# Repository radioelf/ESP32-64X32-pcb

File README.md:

# ESP32-64X32-pcb
PCB para conectar un ESP32 (ESP32-DevKitC) a un panel de 64x32 pixels (p5(2121)-16S-6432-B0), siguiendo
el proyecto de [domótica fácil con Jota](https://www.youtube.com/channel/UC61-AfFnspjffs71zmmn2Ig)

Creative Commons License Disclaimer

UNLESS OTHERWISE MUTUALLY AGREED TO BY THE PARTIES IN WRITING, LICENSOR OFFERS THE WORK AS-IS AND MAKES NO REPRESENTATIONS OR WARRANTIES OF ANY KIND CONCERNING THE WORK, EXPRESS, IMPLIED, STATUTORY OR OTHERWISE, INCLUDING, WITHOUT LIMITATION, WARRANTIES OF TITLE, MERCHANTIBILITY, FITNESS FOR A PARTICULAR PURPOSE, NONINFRINGEMENT, OR THE ABSENCE OF LATENT OR OTHER DEFECTS, ACCURACY, OR THE PRESENCE OF ABSENCE OF ERRORS, WHETHER OR NOT DISCOVERABLE. SOME JURISDICTIONS DO NOT ALLOW THE EXCLUSION OF IMPLIED WARRANTIES, SO SUCH EXCLUSION MAY NOT APPLY TO YOU. EXCEPT TO THE EXTENT REQUIRED BY APPLICABLE LAW, IN NO EVENT WILL LICENSOR BE LIABLE TO YOU ON ANY LEGAL THEORY FOR ANY SPECIAL, INCIDENTAL, CONSEQUENTIAL, PUNITIVE OR EXEMPLARY DAMAGES ARISING OUT OF THIS LICENSE OR THE USE OF THE WORK, EVEN IF LICENSOR HAS BEEN ADVISED OF THE POSSIBILITY OF SUCH DAMAGES.

http://creativecommons.org/licenses/by-sa/3.0/

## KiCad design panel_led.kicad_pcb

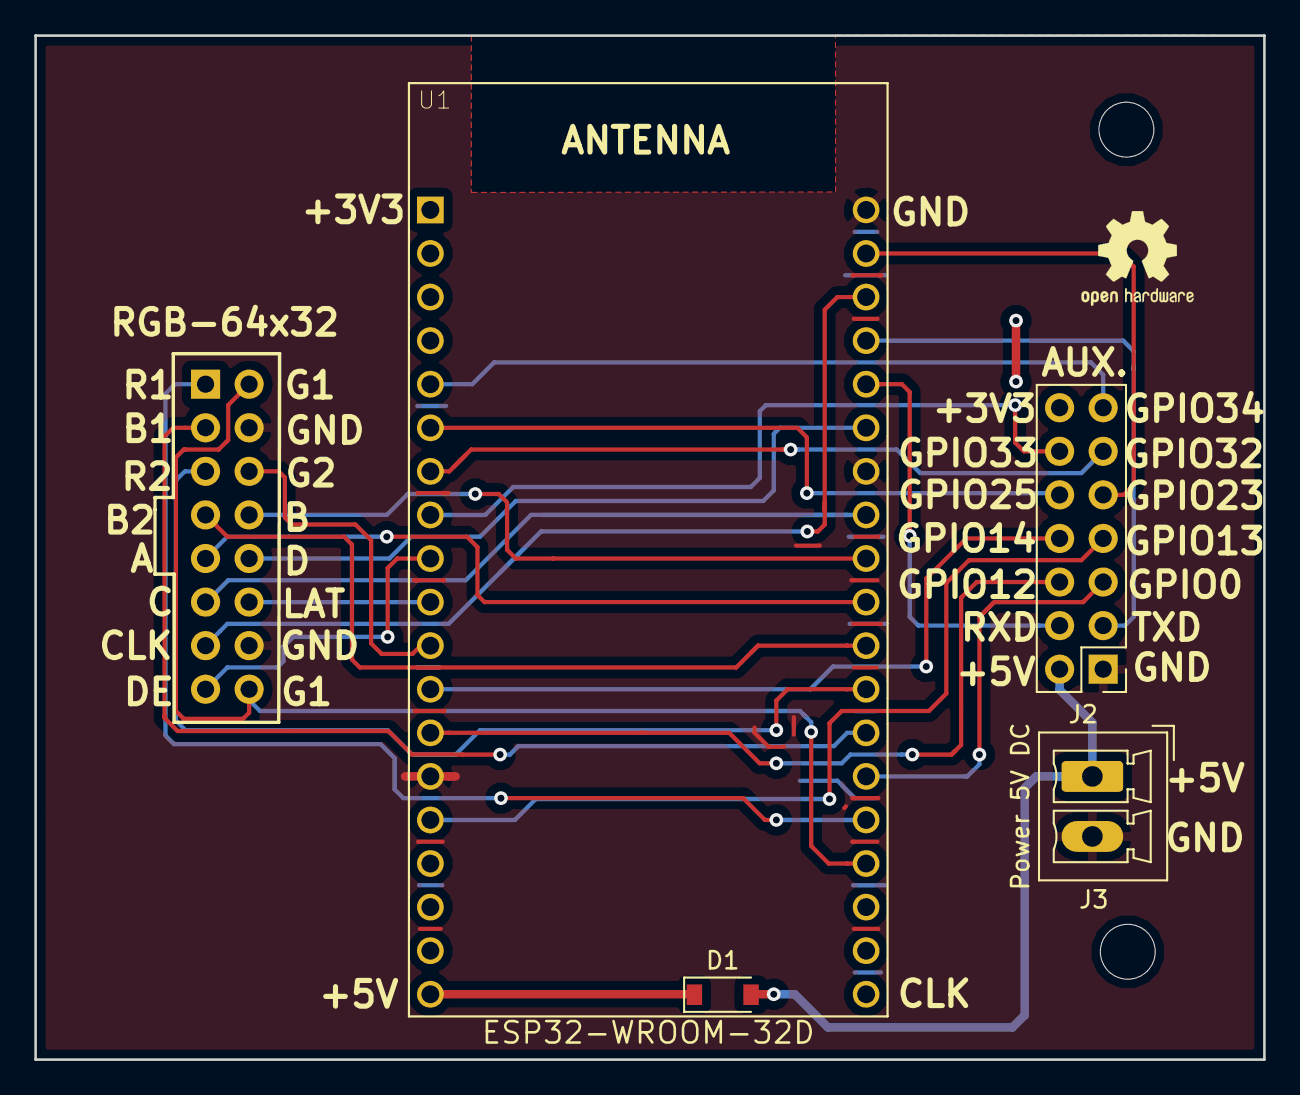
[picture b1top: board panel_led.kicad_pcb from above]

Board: 2 copper layers, 71.6 x 59.7 mm, 5 parts (1 on the bottom side), 28 nets.

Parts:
D1: 1N5819; D_SOD-123
J1: 02x08; PinSocket_2x08_P2.54mm_Vertical
J2: 02x07; PinHeader_2x07_P2.54mm_Vertical
J3: Power 5V DC; PhoenixContact_MCV_1,5_2-G-3.5_1x02_P3.50mm_Vertical
U1: ESP32-WROOM-32D; MODULE_ESP32-DEVKITC-32D

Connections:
+3V3: J2.14, U1.1
+5V: D1.2, J2.2, J3.1
/A: J1.9, U1.29
/B: J1.8, U1.28
/B1: J1.3, U1.32
/B2: J1.7, U1.30
/C: J1.11, U1.27
/CLK: J1.13, U1.22
/D: J1.10, U1.25
/DE: J1.15, U1.9
/G1: J1.2, J1.16, U1.35
/G2: J1.6, U1.11
/LAT: J1.12, U1.10
/R1: J1.1, U1.34
/R2: J1.5, U1.31
GND: J1.4, J1.14, J2.1, J3.2, U1.14, U1.20, U1.26
GPIO0: J2.5, U1.33
GPIO12: J2.6, U1.13
GPIO13: J2.7, U1.15
GPIO14: J2.8, U1.12
GPIO23: J2.9, U1.21
GPIO25: J2.10, U1.6
GPIO32: J2.11, U1.7
GPIO33: J2.12, U1.8
GPIO34: J2.13, U1.5
unnamed: D1.1, U1.19
RXD: J2.4, U1.24
TXD: J2.3, U1.23

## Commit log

2020-08-25 Create NOconfig
2020-08-25 Create SIconfig
